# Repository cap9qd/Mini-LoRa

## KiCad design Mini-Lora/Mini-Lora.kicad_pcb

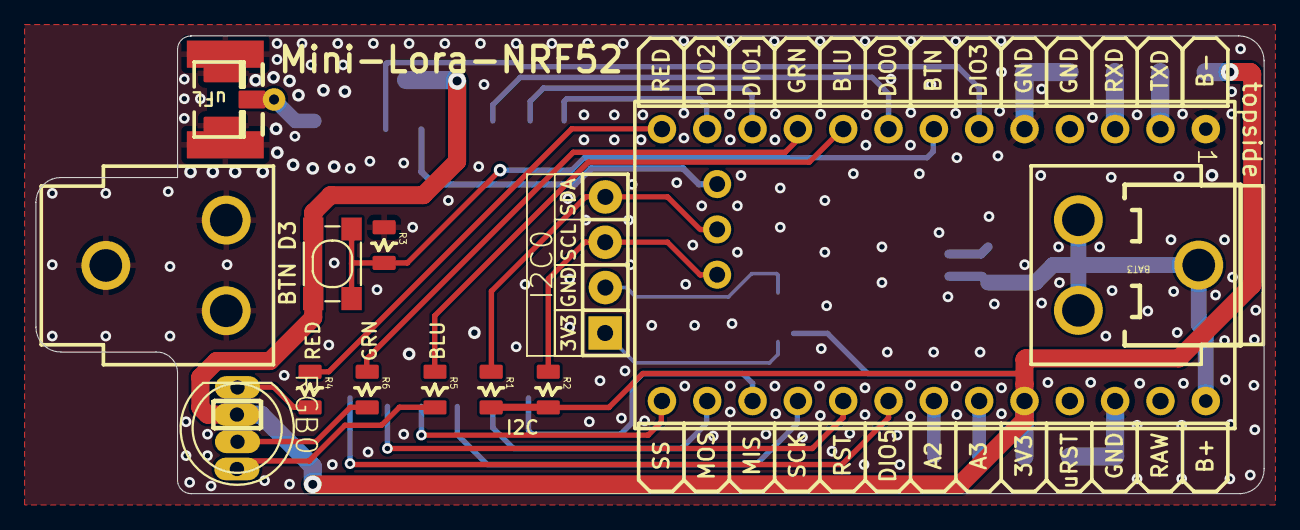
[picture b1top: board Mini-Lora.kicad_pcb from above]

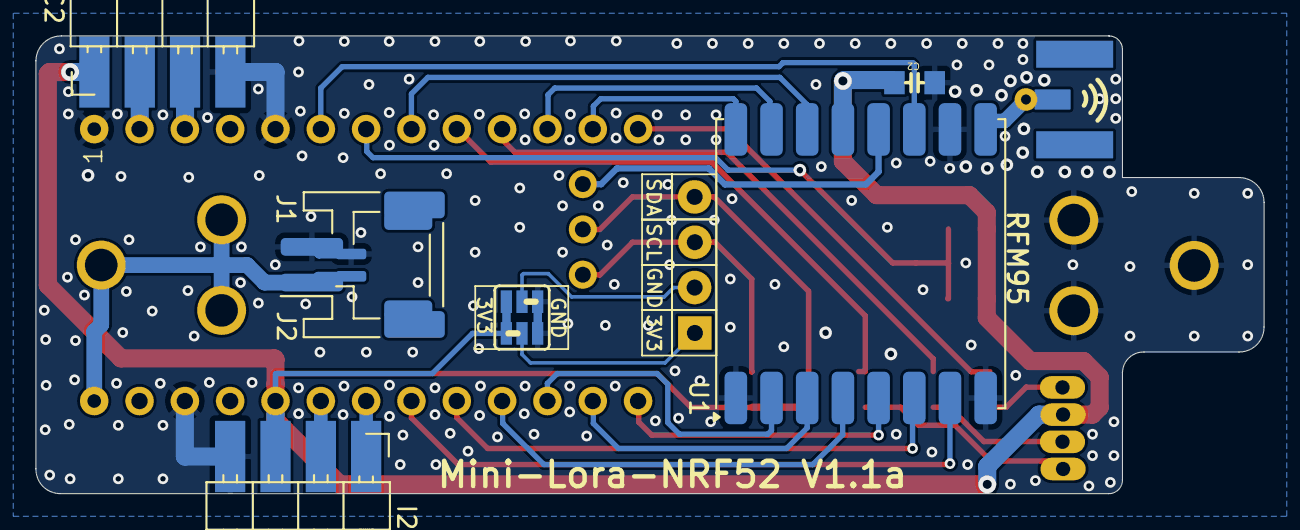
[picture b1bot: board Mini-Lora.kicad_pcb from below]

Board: 2 copper layers, 68.8 x 25.7 mm, 19 parts (7 on the bottom side), 30 nets.

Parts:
BAT3: 18650; BATTERY_18650-HOLDER
BTN0: DHT-4235A; SW4-SMD-4.2X3.2X2.5MM
C2: 10uF; 0805-CAP-LARGEPADS
I2C0: CON_HEADER_1X04'NO_LOCK'; 1X04_NO_LOCK
I2C1, I2C2: CON_HEADER_1X04'NO_LOCK'; PinHeader_1x04_P2.54mm_Horizontal_SMD
J1: BATT; JST_PH_S2B-PH-SM4-TB_1x02-1MP_P2.00mm_Horizontal
J2: BATT; JST_GH_SM02B-GHS-TB_1x02-1MP_P1.25mm_Horizontal
J$2: ANTENNATINY; SMA_UFL_PAD_TINY
MOD1: SuperMini NRF52840
R1, R2: 4.7K; 0805-RES
R3: 10K; 0805-RES
R4: 220; 0805-RES
R5, R6: 100; 0805-RES
RGB0: RGBLED; LED5MMRGB_ST
U1: RFM95W-915S2; HOPERF_RFM9XW_SMD
U$1: PAD-JUMPER-SWAPSWAP; PAD-JUMPER-SWAP

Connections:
+3V3: BTN0.1 (A0), BTN0.2 (A1), C2.2, I2C1.3, I2C2.1, MOD1.22 (VCC), R1.2, R2.2, RGB0.2 (VCC), U1.13 (3.3V), U$1.4
+BATT: BAT3.PWR (+), J1.1, J2.1, MOD1.26 (BAT+)
/A2: I2C1.1, MOD1.20 (P0.29)
/A3: I2C1.2, MOD1.21 (P0.31)
/BLUE: MOD1.9 (P0.24), R5.1
/D3: BTN0.3 (B0), BTN0.4 (B1), MOD1.7 (P0.20), R3.2
/DIO0: MOD1.8 (P0.22), U1.14 (DIO0)
/DIO1: MOD1.11 (P0.11), U1.15 (DIO1)
/DIO2: MOD1.12 (P1.04), U1.16 (DIO2)
/DIO3: MOD1.6 (P0.17), U1.11 (DIO3)
/DIO4: MOD1.27 (P1.01), U1.12 (DIO4)
/DIO5: MOD1.19 (P0.02), U1.7 (DIO5)
/GREEN: MOD1.10 (P1.00), R6.1
/MISO: MOD1.16 (P1.11), U1.2 (MISO)
/MOSI: MOD1.15 (P1.10), U1.3 (MOSI)
/RED: MOD1.13 (P1.06), R4.1
/RESET: MOD1.18 (P1.15), U1.6 (RESET)
/RX: I2C2.3, MOD1.3 (P0.08)
/SCK: MOD1.17 (P1.13), U1.4 (SCK)
/SCL: I2C0.3, MOD1.29 (P1.07), R2.1
/SDA: I2C0.4, MOD1.28 (P1.02), R1.1
/SS: MOD1.14 (P0.09), U1.5 (NSS)
/TX: I2C2.2, MOD1.2 (P0.06)
GND: BAT3.GND (-), C2.1, I2C1.4, I2C2.4, J1.2, J2.2, J$2.GND1 (GND@0), J$2.GND2 (GND@1), J$2.GND3 (GND@2), J$2.GND4 (GND@3), MOD1.1 (BAT-), MOD1.5 (GND), MOD1.24 (GND), R3.1, U1.1 (GND), U1.8 (GND), U1.10 (GND), U$1.1
unnamed: I2C0.1, U$1.3
unnamed: I2C0.2, U$1.2
unnamed: R5.2, RGB0.4 (BLUE)
unnamed: R6.2, RGB0.3 (GREEN)
unnamed: R4.2, RGB0.1 (RED)
unnamed: J$2.ANT1 (SIGNAL), J$2.ANT2 (SIGNAL), J$2.ANT3 (SIGNAL), U1.9 (ANT)

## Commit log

2024-11-27 Converted to KiCAD and updated layout for ProMicro NRF52840
2024-11-27 Update to schematic.
2024-11-27 More updates before fab
2025-01-10 KiCAD backups...
